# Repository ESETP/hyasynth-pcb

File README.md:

# hayasynth-pcb
PCB for hayasynth

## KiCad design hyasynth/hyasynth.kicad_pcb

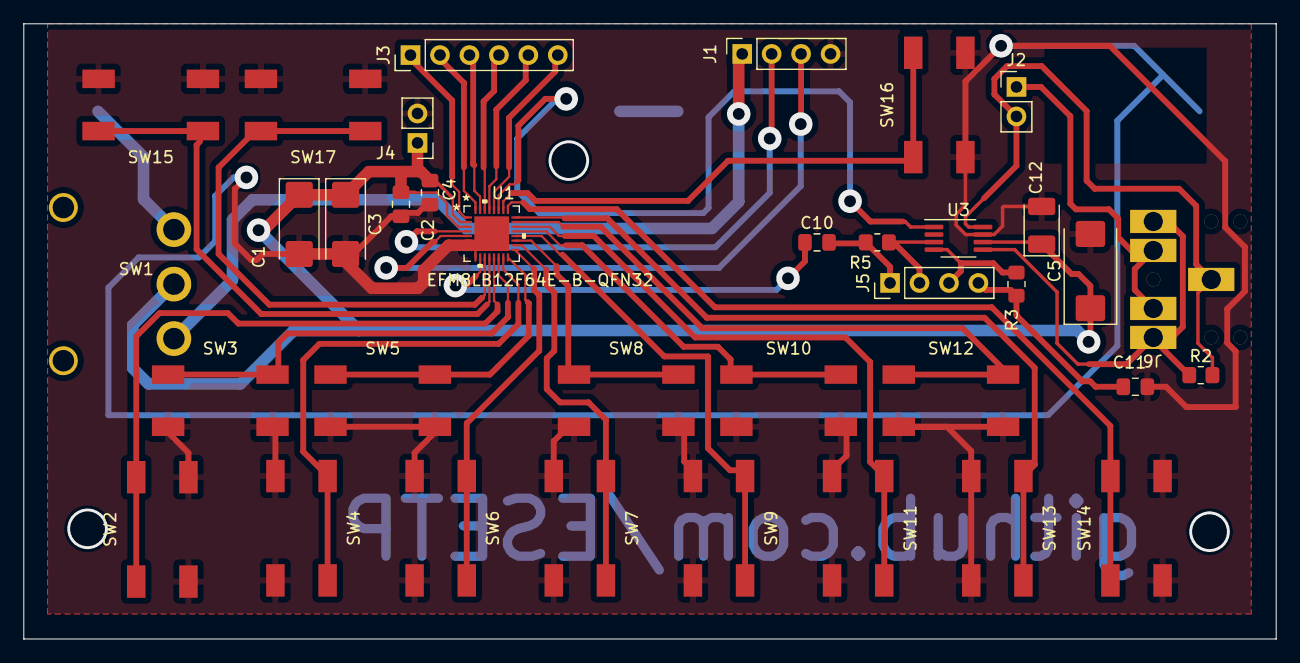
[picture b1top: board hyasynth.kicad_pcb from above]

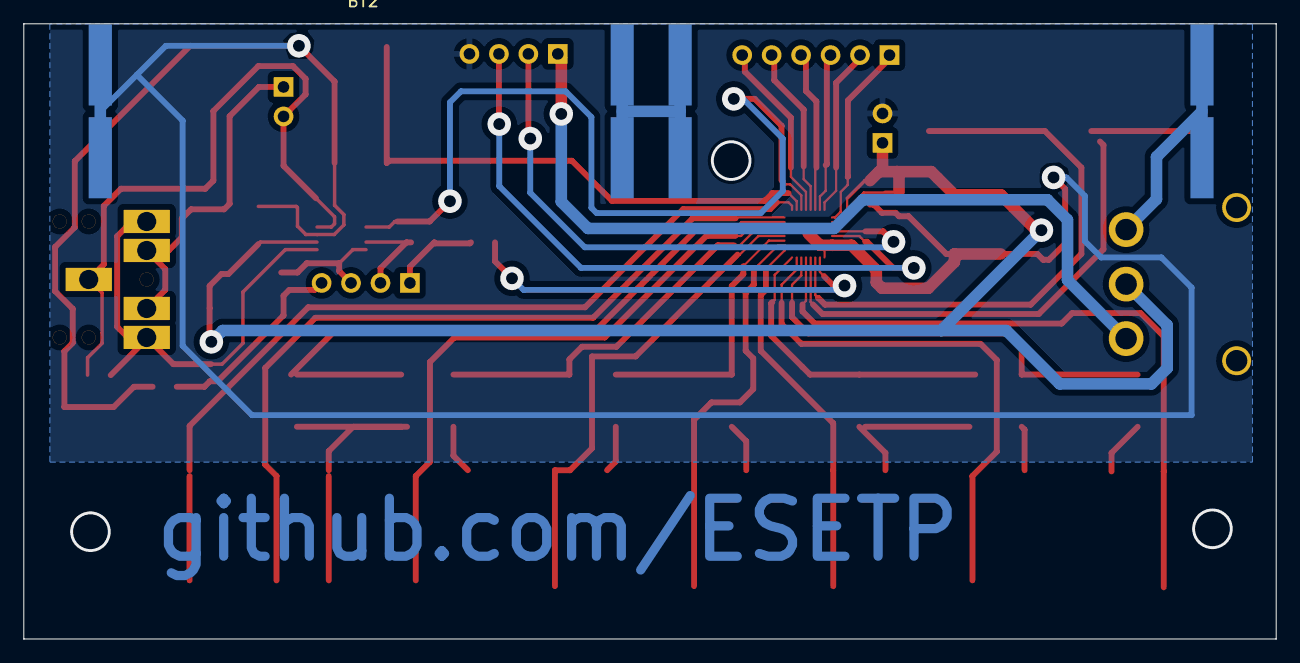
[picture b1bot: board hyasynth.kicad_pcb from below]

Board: 2 copper layers, 108.0 x 53.0 mm, 38 parts (2 on the bottom side), 38 nets.

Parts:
BT1, BT2: Battery_Cell; Battery AAA
C1, C3: 4.7u; CP_EIA-6032-28_Kemet-C_Pad2.25x2.35mm_HandSolder
C2, C4, C10, C11: 0.1u; C_0805_2012Metric_Pad1.18x1.45mm_HandSolder
C5: 10u; CP_EIA-7343-31_Kemet-D_Pad2.25x2.55mm_HandSolder
C12: 1u; CP_EIA-3528-12_Kemet-T_Pad1.50x2.35mm_HandSolder
J1: Conn_01x04_Male; PinSocket_1x04_P2.54mm_Vertical
J2, J4: Conn_01x02_Male; PinHeader_1x02_P2.54mm_Vertical
J3: Conn_01x06_Male; PinHeader_1x06_P2.54mm_Vertical
J5: Conn_01x04_Male; PinHeader_1x04_P2.54mm_Vertical
J6: AudioJack3_SwitchTR; Jack
R2: 8; R_0805_2012Metric_Pad1.20x1.40mm_HandSolder
R3, R5: R; R_0805_2012Metric_Pad1.20x1.40mm_HandSolder
SW1: Power Switch; Slide Switch
SW2: Low C; SW_Push_hand_solder
SW3: C# Db; SW_Push_hand_solder
SW4: D; SW_Push_hand_solder
SW5: D# Eb; SW_Push_hand_solder
SW6: E; SW_Push_hand_solder
SW7: F; SW_Push_hand_solder
SW8: F# Gb; SW_Push_hand_solder
SW9: G; SW_Push_hand_solder
SW10: G# Ab; SW_Push_hand_solder
SW11: A; SW_Push_hand_solder
SW12: A# Bb; SW_Push_hand_solder
SW13: B; SW_Push_hand_solder
SW14: C; SW_Push_hand_solder
SW15: Down Octave; SW_Push_hand_solder
SW16: Function; SW_Push_hand_solder
SW17: Up Octave; SW_Push_hand_solder
U1: EFM8LB12F64E-B-QFN32
U3: PAM8302AAD; MSOP-8_3x3mm_P0.65mm

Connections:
/A: SW11.2, U1.22 (P1-3)
/A#: SW12.2, U1.23 (P1-2)
/AMP_OUT+: J6.2 (R), J6.5 (T), R2.1, U3.5 (OUT+)
/AMP_OUT-: J2.2, J6.1 (S), R2.2, U3.8 (OUT-)
/AMP_SD: U1.27 (P0-6), U3.1 (~SD)
/B: SW13.2, U1.24 (P1-1)
/C: SW14.2, U1.25 (P1-0)
/C2CLK: J1.2, U1.4 (RSTB/C2CK)
/C2D: J1.3, U1.5 (P3-7/C2D)
/C#: SW3.2, U1.14 (P2-3)
/D: SW4.2, U1.15 (P2-2)
/D#: SW5.2, U1.16 (P2-1)
/DAC: C10.1, U1.10 (P3-0)
/Debug_Power: J1.1, SW1.1 (A)
/Down: SW15.2, U1.12 (P2-5)
/E: SW6.2, U1.17 (P2-0)
/F: SW7.2, U1.18 (P1-7)
/F#: SW8.2, U1.19 (P1-6)
/Function: SW16.2, U1.26 (P0-7)
/G: SW9.2, U1.20 (P1-5)
/G#: SW10.2, U1.21 (P1-4)
/GPIO_1: J3.4, U1.30 (P0-3)
/GPIO_2: J3.3, U1.31 (P0-2)
/GPIO_3: J3.2, U1.32 (P0-1)
/GPIO_4: J3.1, U1.1 (P0-0)
/Low_C: SW2.2, U1.13 (P2-4)
/SPK_OUT-: J2.1, J6.3 (RN), J6.4 (Tn)
/Uart_RX: J3.6, U1.28 (P0-5)
/Uart_TX: J3.5, U1.29 (P0-4)
/Up: SW17.2, U1.11 (P2-6)
/V_pot_in: C10.2, J5.1, R5.1
/V_pot_minus_in: C11.2, J5.4, R3.1
/V_pot_minus_out: J5.3, R3.2, U3.4 (IN-)
/V_pot_out: J5.2, R5.2, U3.3 (IN+)
GND: BT2.2 (-), C1.2, C2.2, C3.2, C4.2, C5.2, C11.1, C12.2, J1.4, J4.2, SW2.1, SW3.1, SW4.1, SW5.1, SW6.1, SW7.1, SW8.1, SW9.1, SW10.1, SW11.1, SW12.1, SW13.1, SW14.1, SW15.1, SW16.1, SW17.1, U1.6 (P3-4), U1.7 (P3-3), U1.8 (P3-2), U1.9 (P3-1), U1.33 (EPAD), U3.7 (GND)
unnamed: BT1.1 (+), SW1.3 (C)
unnamed: BT1.2 (-), BT2.1 (+)
VDD: C1.1, C2.1, C3.1, C4.1, C5.1, C12.1, J4.1, SW1.2 (B), U1.2 (VIO), U1.3 (VDD), U3.6 (VDD)

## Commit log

2022-01-12 Added Kicad project
2022-01-20 started schematic, micro, power placed, started rst/flashing
2022-01-22 Keep backups local since git
2022-01-22 Added Keybaord to schematic
2022-01-22 Neatened up schematic
2022-01-22 Attached footprints to most things
2022-01-25 Made changes to the schematic to fix bugs
2022-01-25 Power Amplifier for speaker output
2022-01-27 Added a jumper
2022-01-27 Added GPIO and LED
2022-01-27 Finished inital schematic design, added second amp, rearranged pins
2022-02-03 Definatly Borked
2022-02-03 Complete Footprint
2022-02-03 Footprint corrected
2022-02-03 Nothing's changed
2022-02-03 started laying out pcb
2022-02-03 Did very little work
2022-02-08 set battery positions, adjusted for caps
2022-02-10 laid out switches, started routing them.
2022-02-24 wired in switches and dac mostly
2022-03-10 finished pcb v1
2022-03-10 final first draft I swear
2022-03-30 Button Library
2022-03-31 Added new footprints
2022-03-31 Change gitignore
2022-03-31 Footprint
2022-03-31 update project footprints table
2022-03-31 Footprint table
2022-03-31 New Footprints
2022-03-31 borrowed new button footprint
2022-04-01 Added jack and switch and repositioned components
2022-04-07 Added thermal relief to battery pads
2022-04-07 Assembly Instructions
2022-04-07 Added more instructions
2022-04-18 Finished Basic Revision of PCB
2022-04-18 Small changes to the direction tracks are going out from ICs in
2022-04-18 Fixed GND via keepout
2022-04-19 Schematic Changes
2022-04-21 Removed Three Vias
2022-04-21 Added PDF to gitignore
2022-04-21 Change Footprint for Button
2022-04-21 Change Footprint for Jack and Switch
2022-04-21 tweaks for printing
2022-04-21 updated for new footprints
2022-05-17 added headphone resistor, moved amp SD pin, tweak hole size
2022-05-17 added github link to copper
2022-05-20 Update AssemblyInstructions.md
    Switched via and resistors and caps position as its easy to bridge power and ground under a cap, which is hard to find with the vias in
2022-05-23 Added logos
2022-05-23 Silkscreen almost complete
2022-05-23 Added 3d models
2022-05-24 Schematic
2022-05-24 changed link to github not website
2022-05-24 Changed to correct github link
2022-05-24 Removed odd
2022-06-21 New Switch and Silkscreen changes
2022-06-25 Changes to silkscreen
2022-06-25 Fab 2
2022-06-28 Fab 3
2022-07-04 Added Holes for fab
2022-07-04 adjusted battery silkscreen position and edge cut for andrew
2022-07-04 also tidied up fab
2024-02-29 Make suitable for fabrication
    - Add load resistor across amp output
    - Add resistor values for amp input
    - Convert edge cuts for drill holes to actual holes
    - Remove debug pad under speaker

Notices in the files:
parts and their libraries:
Copyright 2021 Accelerated Designs. All rights reserved.
